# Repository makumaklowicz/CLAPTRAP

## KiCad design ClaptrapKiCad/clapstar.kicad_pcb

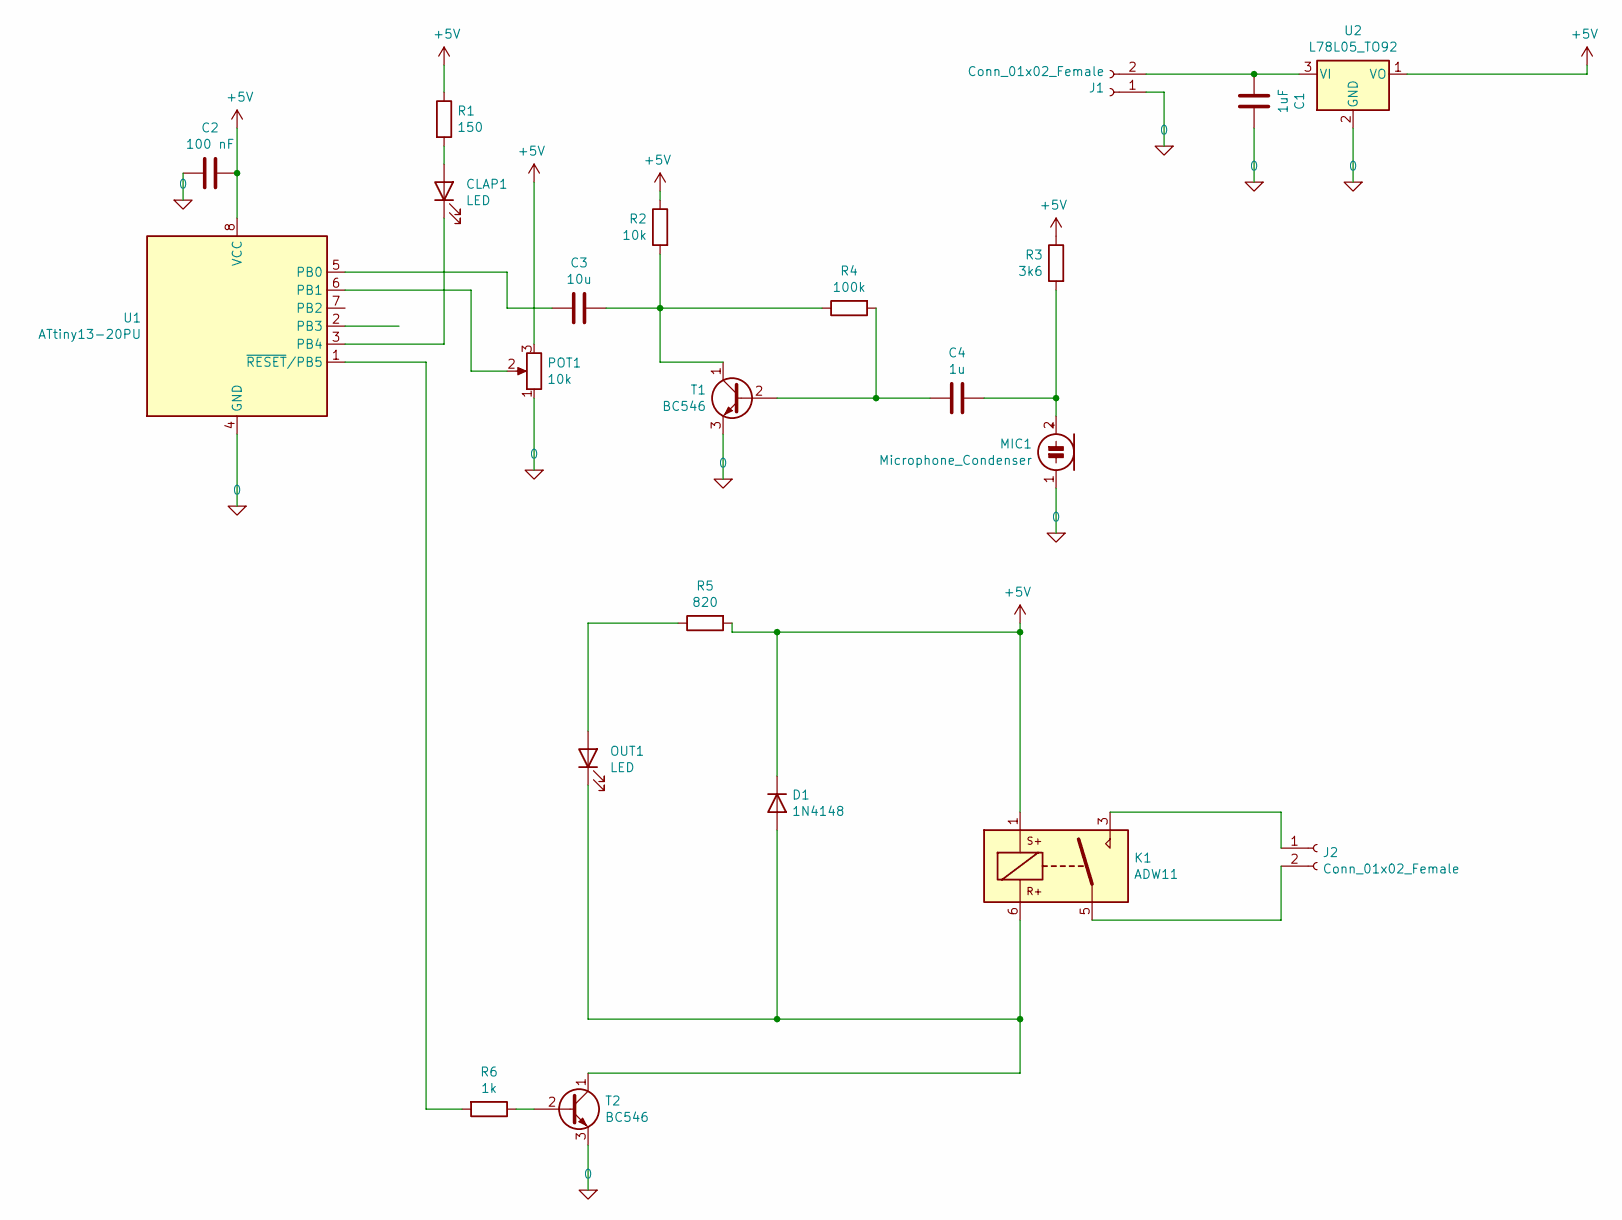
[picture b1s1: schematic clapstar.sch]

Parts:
C1: 1uF; C_Disc_D4.7mm_W2.5mm_P5.00mm
C2: 100 nF; C_Disc_D3.0mm_W2.0mm_P2.50mm
C3: 10u; CP_Radial_D5.0mm_P2.50mm
C4: 1u; C_Disc_D4.7mm_W2.5mm_P5.00mm
CLAP1: LED; LED_D3.0mm
D1: 1N4148; D_DO-35_SOD27_P7.62mm_Horizontal
J1: Conn_01x02_Female; SolderWire-0.1sqmm_1x02_P3.6mm_D0.4mm_OD1mm_Relief
J2: Conn_01x02_Female; TerminalBlock_Altech_AK300-2_P5.00mm
K1: ADW11; Relay_1P1T_NO_10x24x18.8mm_Panasonic_ADW11xxxxW_THT
MIC1: Microphone_Condenser; SolderWire-0.1sqmm_1x02_P3.6mm_D0.4mm_OD1mm
OUT1: LED; LED_D3.0mm
POT1: 10k; Potentiometer_Vishay_T73YP_Vertical
R1: 150; R_Axial_DIN0207_L6.3mm_D2.5mm_P10.16mm_Horizontal
R2: 10k; R_Axial_DIN0207_L6.3mm_D2.5mm_P10.16mm_Horizontal
R3: 3k6; R_Axial_DIN0207_L6.3mm_D2.5mm_P10.16mm_Horizontal
R4: 100k; R_Axial_DIN0207_L6.3mm_D2.5mm_P10.16mm_Horizontal
R5: 820; R_Axial_DIN0207_L6.3mm_D2.5mm_P10.16mm_Horizontal
R6: 1k; R_Axial_DIN0207_L6.3mm_D2.5mm_P10.16mm_Horizontal
T1, T2: BC546; TO-92_Inline
U1: ATtiny13-20PU; DIP-8_W7.62mm
U2: L78L05_TO92; TO-92_Inline

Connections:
0: C1.1, C2.2, J1.1, MIC1.1 (-), POT1.1, T1.3 (E), T2.3 (E), U1.4 (GND), U2.2 (GND)
+5V: C2.1, D1.1 (K), K1.1, POT1.3, R1.1, R2.1, R3.1, R5.2, U1.8 (VCC), U2.1 (VO)
unnamed: C1.2, J1.2, U2.3 (VI)
unnamed: C3.1, U1.5 (PB0)
unnamed: C3.2, R2.2, R4.1, T1.1 (C)
unnamed: C4.1, R4.2, T1.2 (B)
unnamed: C4.2, MIC1.2 (+), R3.2
unnamed: CLAP1.1 (K), U1.3 (PB4)
unnamed: CLAP1.2 (A), R1.2
unnamed: D1.2 (A), K1.6, OUT1.1 (K), T2.1 (C)
unnamed: J2.1, K1.3
unnamed: J2.2, K1.5
unnamed: OUT1.2 (A), R5.1
unnamed: POT1.2, U1.6 (PB1)
unnamed: R6.1, T2.2 (B)
unnamed: R6.2, U1.1 (~RESET~/PB5)

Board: 2 copper layers, 22 parts (0 on the bottom side), 16 nets, no tracks yet.

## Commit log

2021-12-12 Bugfix: Added connection (Transistor T1)
2021-12-12 Renamed files, trash deleted
2021-12-12 Trash deleted
2021-12-15 Added: KiCad design files
2022-01-09 Added: PCB Design sketch, Dane.txt
2022-01-24 Added report
2022-01-24 Updated: Dane.txt
2022-01-31 Raport updated
2022-01-31 Updated: Dane.txt (numery indeksów, samoocena)
